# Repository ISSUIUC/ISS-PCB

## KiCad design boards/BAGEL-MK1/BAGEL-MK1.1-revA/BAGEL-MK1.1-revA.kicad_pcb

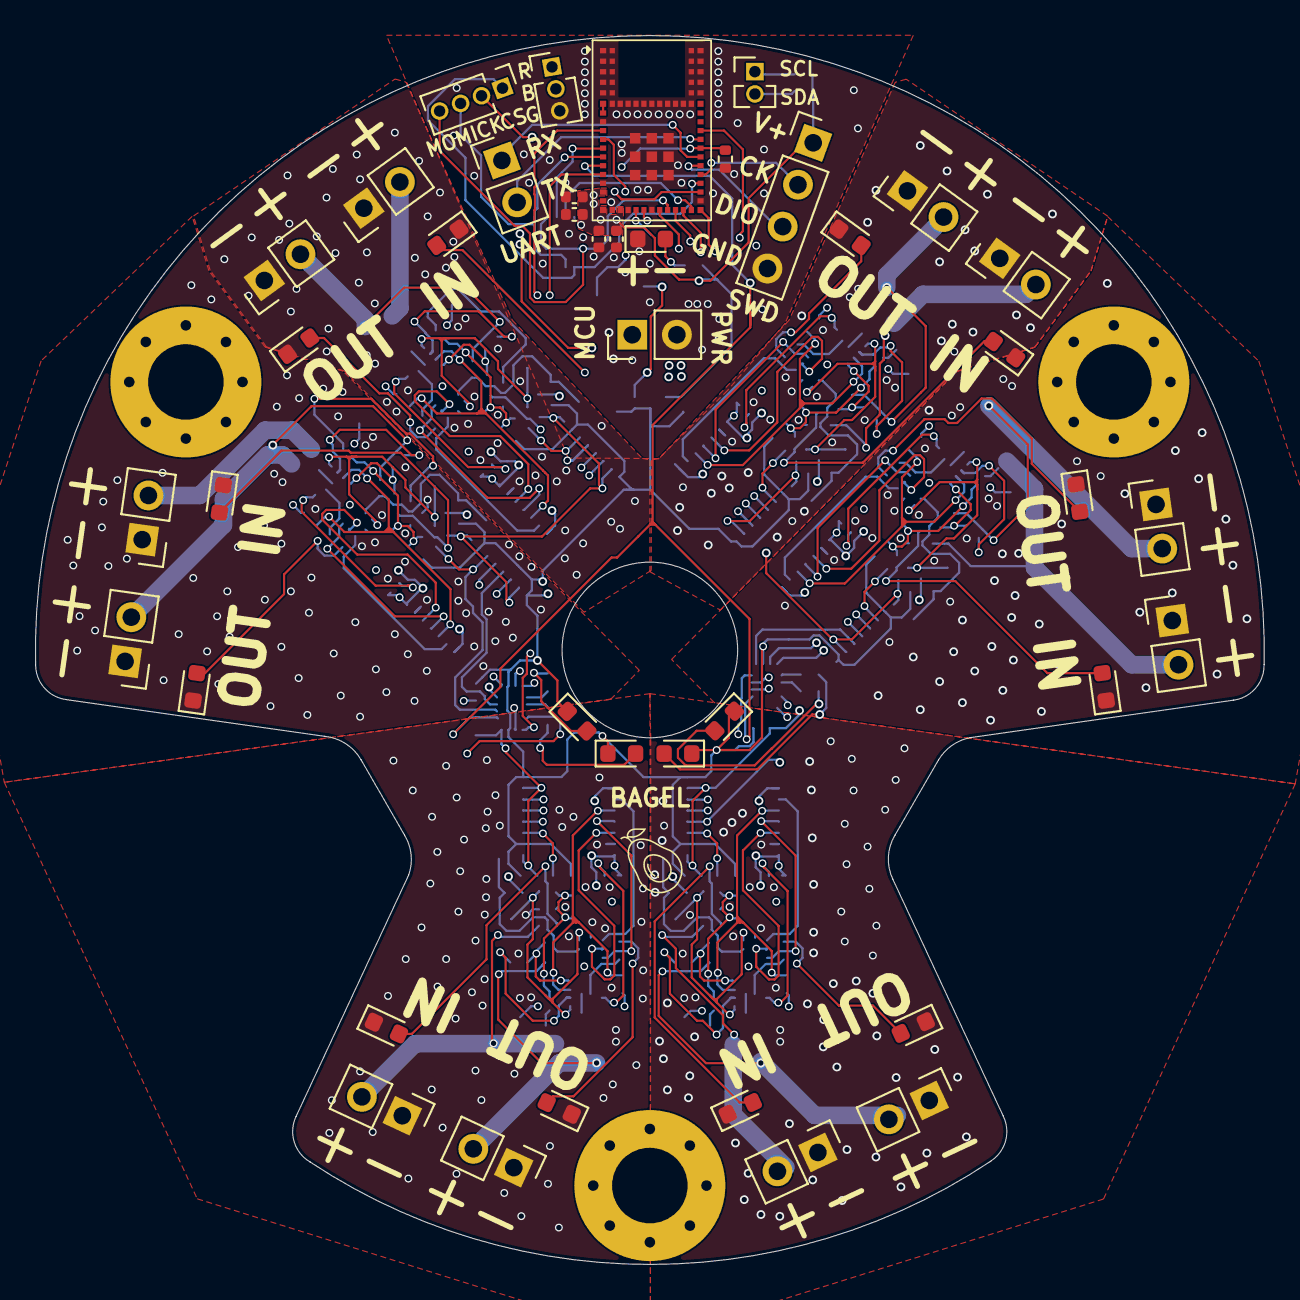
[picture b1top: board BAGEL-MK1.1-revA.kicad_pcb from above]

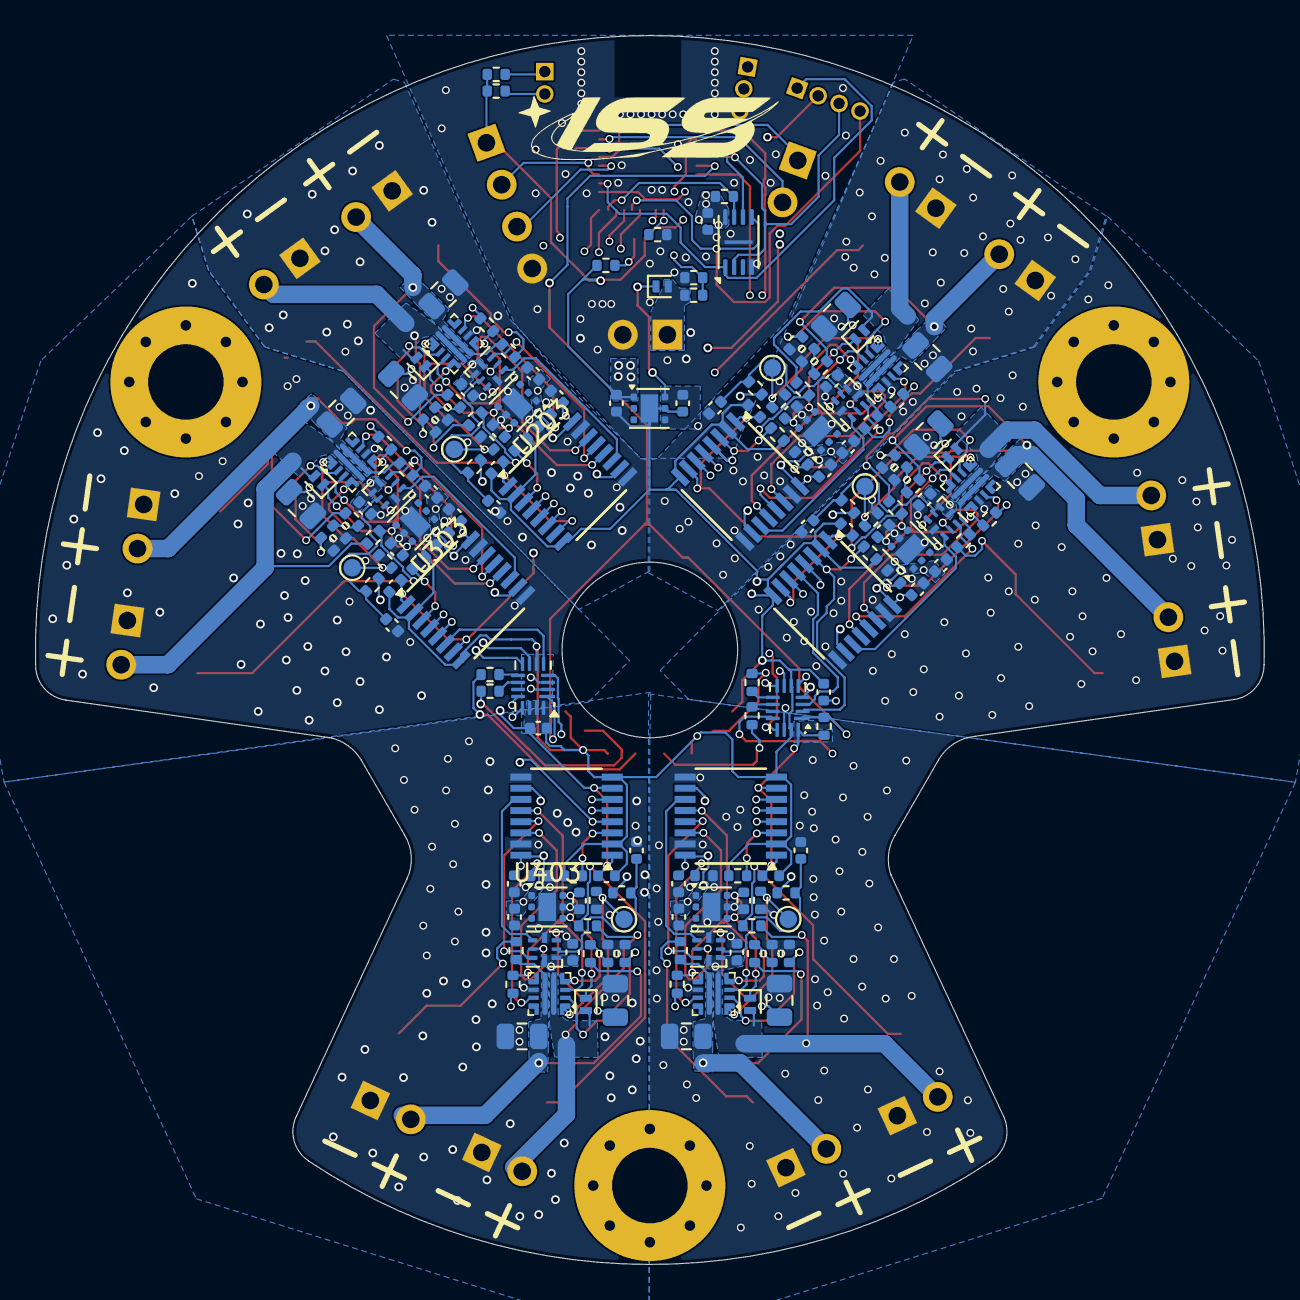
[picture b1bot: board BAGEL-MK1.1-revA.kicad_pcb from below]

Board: 4 copper layers, 70.0 x 70.0 mm, 210 parts (166 on the bottom side), 144 nets.

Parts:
C101, C103, C104, C105, C108, C109, C201, C202, C203, C207, C301, C302, C303, C307, C401, C402, C403, C407, C501, C502, C503, C507, C601, C602, C603, C607, C701, C702, C703, C707: 100nF; C_0402_1005Metric
C102: 4.7uF; C_0402_1005Metric
C106, C204, C304, C404, C504, C604, C704: 1uF; C_0402_1005Metric
C107, C205, C305, C405, C505, C605, C705: 2.2uF; C_0402_1005Metric
C206, C306, C406, C506, C606, C706: 100uF; C_0805_2012Metric
C208, C308, C408, C508, C608, C708: 22uF; C_0805_2012Metric
D101, D201, D301, D401, D501, D601, D701: SDM05U40CSP-7; D_SOD-882
D102, D103, D202, D302, D402, D502, D602, D702: RED; LED_0603_1608Metric
D104: ORANGE; LED_0603_1608Metric
D105, D203, D303, D403, D503, D603, D703: GREEN; LED_0603_1608Metric
D106: BLUE; LED_0603_1608Metric
H101, H102, H103: MountingHole_Pad; MountingHole_4.3mm_M4_Pad_Via
J101, J102, J103, J104, J105, J106, J109, J110, J113, J114, J115, J116, J117, J118: Conn_01x02; PinHeader_1x02_P2.54mm_Vertical
J107: Conn_01x03; PinHeader_1x03_P1.27mm_Vertical
J108: Conn_01x04; PinHeader_1x04_P2.54mm_Vertical
J111: Conn_01x02; PinHeader_1x02_P1.27mm_Vertical
J112: Conn_01x04; PinHeader_1x04_P1.27mm_Vertical
J201, J301, J401, J501, J601, J701: Conn_01x01; TestPoint_Pad_D1.0mm
R101, R102, R103, R113, R201, R202, R204, R205, R301, R302, R304, R305, R401, R402, R404, R405, R501, R502, R504, R505, R601, R602, R604, R605, R701, R702, R704, R705: 10k; R_0402_1005Metric
R104, R105, R106, R107, R108, R109, R112, R203, R303, R403, R503, R603, R703: 4.7k; R_0402_1005Metric
R110, R111: 100k; R_0402_1005Metric
R206, R306, R406, R506, R606, R706: 680; R_0402_1005Metric
R207, R307, R407, R507, R607, R707: 390k; R_0402_1005Metric
R208, R308, R408, R508, R608, R708: 300k; R_0402_1005Metric
R209, R309, R409, R509, R609, R709: 500k; R_0402_1005Metric
R210, R310, R410, R510, R610, R710: 1k; R_0402_1005Metric
U101: W25Q16JLUX; Winbond_USON-8-1EP_3x2mm_P0.5mm_EP0.2x1.6mm
U102: STM32WB1MMC; LGA77_6P5X10_STM
U103, U203, U303, U403, U503, U603, U703: TPS7A25; WSON-6-1EP_2x2mm_P0.65mm_EP1x1.6mm
U104, U105: TCAL9538; UQFN-16_1.8x2.6mm_P0.4mm
U201, U301, U401, U501, U601, U701: ISO7742; SSOP-16_3.9x4.9mm_P0.635mm
U202, U302, U402, U502, U602, U702: SN74AUP1G74RSER; UQFN-RSE0008A
U204, U304, U404, U504, U604, U704: TPS25947; VQFN-HR-RPW0010A

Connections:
/BLUE_LED: R108.1, U105.10 (P7)
/BOOT: J107.2, R102.2, U102.22 (BOOT0)
/CoinCell_V: D101.2 (A), J109.1, R110.2
/EXP_RESET: R103.1, U102.13 (PA2), U104.1 (~RESET), U105.1 (~RESET)
/FLASH_CS: J112.1, U101.1 (~CS), U102.33 (PB4)
/FLASH_RESET: R101.2, U101.7 (~HOLD/~RESET/IO_{3}), U102.29 (PA7)
/GPIO_Clock: R113.2, U102.37 (PA0), U201.4 (INB), U301.4 (INB), U401.4 (INB), U501.4 (INB), U601.4 (INB), U701.4 (INB)
/GREEN_LED: R107.1, U105.9 (P6)
/I2C_SCL: J111.1, R112.1, U102.27 (PB6), U104.12 (SCL), U105.12 (SCL)
/I2C_SDA: J111.2, R109.1, U102.25 (PB7), U104.13 (SDA), U105.13 (SDA)
/NRST: J107.1, U102.23 (NRST)
/ORANGE_LED: R106.1, U104.10 (P7)
/PG_ISO_1: U102.28 (PA3), U201.5 (OUTC)
/PG_ISO_2: U104.7 (P4), U301.5 (OUTC)
/PG_ISO_3: U104.3 (P1), U401.5 (OUTC)
/PG_ISO_4: U105.7 (P4), U501.5 (OUTC)
/PG_ISO_5: U105.3 (P1), U601.5 (OUTC)
/PG_ISO_6: U102.9 (PA4), U701.5 (OUTC)
/RED_LED: R105.1, U104.9 (P6)
/SPI_MISO: J112.3, U101.2 (DO/IO_{1}), U102.12 (PA6)
/SPI_MOSI: J112.4, U101.5 (DI/IO_{0}), U102.26 (PB5)
/SPI_SCK: J112.2, U101.6 (CLK), U102.11 (PA1)
/SWCLK: J108.2, U102.34 (PA14)
/SWDIO: J108.3, U102.35 (PA13)
/SubBatt_GND1: C201.2, C203.2, C204.2, C205.2, C206.2, C207.1, C208.2, D202.1 (K), D203.1 (K), J101.1, J102.1, R202.1, R206.1, R207.2, R209.2, U201.9 (GND2), U201.15 (GND2), U202.4 (GND), U203.5 (GND), U203.7 (Thermal), U204.8 (GND)
/SubBatt_GND2: C301.2, C303.2, C304.2, C305.2, C306.2, C307.1, C308.2, D302.1 (K), D303.1 (K), J103.1, J104.1, R302.1, R306.1, R307.2, R309.2, U301.9 (GND2), U301.15 (GND2), U302.4 (GND), U303.5 (GND), U303.7 (Thermal), U304.8 (GND)
/SubBatt_GND3: C401.2, C403.2, C404.2, C405.2, C406.2, C407.1, C408.2, D402.1 (K), D403.1 (K), J105.1, J106.1, R402.1, R406.1, R407.2, R409.2, U401.9 (GND2), U401.15 (GND2), U402.4 (GND), U403.5 (GND), U403.7 (Thermal), U404.8 (GND)
/SubBatt_GND4: C501.2, C503.2, C504.2, C505.2, C506.2, C507.1, C508.2, D502.1 (K), D503.1 (K), J113.1, J114.1, R502.1, R506.1, R507.2, R509.2, U501.9 (GND2), U501.15 (GND2), U502.4 (GND), U503.5 (GND), U503.7 (Thermal), U504.8 (GND)
/SubBatt_GND5: C601.2, C603.2, C604.2, C605.2, C606.2, C607.1, C608.2, D602.1 (K), D603.1 (K), J115.1, J116.1, R602.1, R606.1, R607.2, R609.2, U601.9 (GND2), U601.15 (GND2), U602.4 (GND), U603.5 (GND), U603.7 (Thermal), U604.8 (GND)
/SubBatt_GND6: C701.2, C703.2, C704.2, C705.2, C706.2, C707.1, C708.2, D702.1 (K), D703.1 (K), J117.1, J118.1, R702.1, R706.1, R707.2, R709.2, U701.9 (GND2), U701.15 (GND2), U702.4 (GND), U703.5 (GND), U703.7 (Thermal), U704.8 (GND)
/SubBatt_V1: D201.2 (A), J101.2, R203.1, U204.5 (IN)
/SubBatt_V2: D301.2 (A), J103.2, R303.1, U304.5 (IN)
/SubBatt_V3: D401.2 (A), J105.2, R403.1, U404.5 (IN)
/SubBatt_V4: D501.2 (A), J113.2, R503.1, U504.5 (IN)
/SubBatt_V5: D601.2 (A), J115.2, R603.1, U604.5 (IN)
/SubBatt_V6: D701.2 (A), J117.2, R703.1, U704.5 (IN)
/Switch 1/PG: R205.2, U201.12 (INC), U204.3 (PG/AUXOFF)
/Switch 1/Q: J201.1, R202.2, U202.3 (Q), U204.1 (EN/UVLO)
/Switch 1/Reg_V: C201.1, C203.1, C205.1, C206.1, R204.1, R205.1, U201.10 (EN2), U201.16 (VCC2), U202.1 (~PRE), U202.8 (VCC), U203.1 (VOUT)
/Switch 1/~CLR: C207.2, R204.2, U202.2 (~CLR)
/Switch 1/~Q: U201.11 (IND), U202.5 (~Q)
/Switch 2/PG: R305.2, U301.12 (INC), U304.3 (PG/AUXOFF)
/Switch 2/Q: J301.1, R302.2, U302.3 (Q), U304.1 (EN/UVLO)
/Switch 2/Reg_V: C301.1, C303.1, C305.1, C306.1, R304.1, R305.1, U301.10 (EN2), U301.16 (VCC2), U302.1 (~PRE), U302.8 (VCC), U303.1 (VOUT)
/Switch 2/~CLR: C307.2, R304.2, U302.2 (~CLR)
/Switch 2/~Q: U301.11 (IND), U302.5 (~Q)
/Switch 3/PG: R405.2, U401.12 (INC), U404.3 (PG/AUXOFF)
/Switch 3/Q: J401.1, R402.2, U402.3 (Q), U404.1 (EN/UVLO)
/Switch 3/Reg_V: C401.1, C403.1, C405.1, C406.1, R404.1, R405.1, U401.10 (EN2), U401.16 (VCC2), U402.1 (~PRE), U402.8 (VCC), U403.1 (VOUT)
/Switch 3/~CLR: C407.2, R404.2, U402.2 (~CLR)
/Switch 3/~Q: U401.11 (IND), U402.5 (~Q)
/Switch 4/PG: R505.2, U501.12 (INC), U504.3 (PG/AUXOFF)
/Switch 4/Q: J501.1, R502.2, U502.3 (Q), U504.1 (EN/UVLO)
/Switch 4/Reg_V: C501.1, C503.1, C505.1, C506.1, R504.1, R505.1, U501.10 (EN2), U501.16 (VCC2), U502.1 (~PRE), U502.8 (VCC), U503.1 (VOUT)
/Switch 4/~CLR: C507.2, R504.2, U502.2 (~CLR)
/Switch 4/~Q: U501.11 (IND), U502.5 (~Q)
/Switch 5/PG: R605.2, U601.12 (INC), U604.3 (PG/AUXOFF)
/Switch 5/Q: J601.1, R602.2, U602.3 (Q), U604.1 (EN/UVLO)
/Switch 5/Reg_V: C601.1, C603.1, C605.1, C606.1, R604.1, R605.1, U601.10 (EN2), U601.16 (VCC2), U602.1 (~PRE), U602.8 (VCC), U603.1 (VOUT)
/Switch 5/~CLR: C607.2, R604.2, U602.2 (~CLR)
/Switch 5/~Q: U601.11 (IND), U602.5 (~Q)
/Switch 6/PG: R705.2, U701.12 (INC), U704.3 (PG/AUXOFF)
/Switch 6/Q: J701.1, R702.2, U702.3 (Q), U704.1 (EN/UVLO)
/Switch 6/Reg_V: C701.1, C703.1, C705.1, C706.1, R704.1, R705.1, U701.10 (EN2), U701.16 (VCC2), U702.1 (~PRE), U702.8 (VCC), U703.1 (VOUT)
/Switch 6/~CLR: C707.2, R704.2, U702.2 (~CLR)
/Switch 6/~Q: U701.11 (IND), U702.5 (~Q)
/Switch_1: R201.1, U102.30 (PA12), U201.3 (INA)
/Switch_2: R301.1, U104.8 (P5), U301.3 (INA)
/Switch_3: R401.1, U104.2 (P0), U401.3 (INA)
/Switch_4: R501.1, U105.8 (P5), U501.3 (INA)
/Switch_5: R601.1, U105.2 (P0), U601.3 (INA)
/Switch_6: R701.1, U102.32 (PA11), U701.3 (INA)
/UART_RX: J110.1, U102.36 (PA10)
/UART_TX: J110.2, U102.38 (PA9)
/V_SENSE: R110.1, R111.2, U102.10 (PA8)
/V_out_1: C208.1, J102.2, R208.1, R210.1, U204.6 (OUT)
/V_out_2: C308.1, J104.2, R308.1, R310.1, U304.6 (OUT)
/V_out_3: C408.1, J106.2, R408.1, R410.1, U404.6 (OUT)
/V_out_4: C508.1, J114.2, R508.1, R510.1, U504.6 (OUT)
/V_out_5: C608.1, J116.2, R608.1, R610.1, U604.6 (OUT)
/V_out_6: C708.1, J118.2, R708.1, R710.1, U704.6 (OUT)
/~Q_ISO_1: U102.39 (PA5), U201.6 (OUTD)
/~Q_ISO_2: U104.5 (P3), U301.6 (OUTD)
/~Q_ISO_3: U104.4 (P2), U401.6 (OUTD)
/~Q_ISO_4: U105.5 (P3), U501.6 (OUTD)
/~Q_ISO_5: U105.4 (P2), U601.6 (OUTD)
/~Q_ISO_6: U102.14 (PB8), U701.6 (OUTD)
MCU_GND: C101.2, C102.2, C103.2, C104.2, C105.2, C106.2, C107.2, C108.2, C109.2, C202.2, C302.2, C402.2, C502.2, C602.2, C702.2, D102.1 (K), D103.1 (K), D104.1 (K), D105.1 (K), D106.1 (K), J107.3, J108.4, J109.2, R102.1, R111.1, R113.1, R201.2, R301.2, R401.2, R501.2, R601.2, R701.2, U101.4 (GND), U101.9 (EP), U102.1 (VSS), U102.2 (VSS), U102.3 (VSS), U102.4 (VSS), U102.5 (VSSRF), U102.8 (VSSRF), U102.15 (VSS), U102.17 (VSS), U102.19 (VSS), U102.21 (VSSSMPS), U102.24 (VSS), U102.31 (VSS), U102.43 (VSS), U102.44 (VSS), U102.45 (VSS), U102.46 (VSS), U102.47 (VSS), U102.48 (VSS), U102.49 (VSS), U102.50 (VSS), U102.51 (VSS), U102.52 (VSS), U102.53 (VSS), U102.54 (VSS), U102.55 (VSS), U102.56 (VSS), U102.57 (VSS), U102.58 (VSS), U102.59 (VSS), U102.60 (VSS), U102.61 (VSS), U102.62 (VSS), U102.63 (VSS), U102.64 (VSS), U102.65 (VSS), U102.66 (VSS), U102.67 (VSS), U102.68 (VSS), U102.69 (VSS), U102.70 (VSS), U102.71 (VSS), U102.72 (VSS), U102.73 (VSS), U102.74 (VSS), U102.75 (VSS), U102.76 (VSS), U102.77 (VSS), U103.5 (GND), U103.7 (Thermal), U104.6 (GND), U104.16 (A1), U105.6 (GND), U105.15 (A0), U201.2 (GND1), U201.8 (GND1), U301.2 (GND1), U301.8 (GND1), U401.2 (GND1), U401.8 (GND1), U501.2 (GND1), U501.8 (GND1), U601.2 (GND1), U601.8 (GND1), U701.2 (GND1), U701.8 (GND1)
MCU_V: C101.1, C102.1, C103.1, C104.1, C105.1, C107.1, C108.1, C109.1, C202.1, C302.1, C402.1, C502.1, C602.1, C702.1, J108.1, R101.1, R103.2, R104.2, R109.2, R112.2, U101.8 (VCC), U102.16 (VDDA), U102.18 (VBAT), U102.20 (VDDSMPS), U103.1 (VOUT), U104.14 (VCC), U104.15 (A0), U105.14 (VCC), U105.16 (A1), U201.1 (VCC1), U201.7 (EN1), U301.1 (VCC1), U301.7 (EN1), U401.1 (VCC1), U401.7 (EN1), U501.1 (VCC1), U501.7 (EN1), U601.1 (VCC1), U601.7 (EN1), U701.1 (VCC1), U701.7 (EN1)
unnamed: C106.1, D101.1 (K), U103.4 (EN), U103.6 (VIN)
unnamed: D102.2 (A), R104.1
unnamed: D103.2 (A), R105.2
unnamed: D104.2 (A), R106.2
unnamed: D105.2 (A), R107.2
unnamed: D106.2 (A), R108.2
unnamed: C204.1, D201.1 (K), U203.4 (EN), U203.6 (VIN)
unnamed: D202.2 (A), R203.2
unnamed: D203.2 (A), R210.2
unnamed: C304.1, D301.1 (K), U303.4 (EN), U303.6 (VIN)
unnamed: D302.2 (A), R303.2
unnamed: D303.2 (A), R310.2
unnamed: C404.1, D401.1 (K), U403.4 (EN), U403.6 (VIN)
unnamed: D402.2 (A), R403.2
unnamed: D403.2 (A), R410.2
unnamed: C504.1, D501.1 (K), U503.4 (EN), U503.6 (VIN)
unnamed: D502.2 (A), R503.2
unnamed: D503.2 (A), R510.2
unnamed: C604.1, D601.1 (K), U603.4 (EN), U603.6 (VIN)
unnamed: D602.2 (A), R603.2
unnamed: D603.2 (A), R610.2
unnamed: C704.1, D701.1 (K), U703.4 (EN), U703.6 (VIN)
unnamed: D702.2 (A), R703.2
unnamed: D703.2 (A), R710.2
unnamed: U102.6 (ANT_IN), U102.7 (ANT_OUT)
unnamed: U201.14 (OUTA), U202.6 (D)
unnamed: U201.13 (OUTB), U202.7 (CLK)
unnamed: R206.2, U204.9 (ILM)
unnamed: R207.1, U204.2 (OVLO/OVCSEL)
unnamed: R208.2, R209.1, U204.4 (PGTH/NFLT)
unnamed: U301.14 (OUTA), U302.6 (D)
unnamed: U301.13 (OUTB), U302.7 (CLK)
unnamed: R306.2, U304.9 (ILM)
unnamed: R307.1, U304.2 (OVLO/OVCSEL)
unnamed: R308.2, R309.1, U304.4 (PGTH/NFLT)
unnamed: U401.14 (OUTA), U402.6 (D)
unnamed: U401.13 (OUTB), U402.7 (CLK)
unnamed: R406.2, U404.9 (ILM)
unnamed: R407.1, U404.2 (OVLO/OVCSEL)
unnamed: R408.2, R409.1, U404.4 (PGTH/NFLT)
unnamed: U501.14 (OUTA), U502.6 (D)
unnamed: U501.13 (OUTB), U502.7 (CLK)
unnamed: R506.2, U504.9 (ILM)
unnamed: R507.1, U504.2 (OVLO/OVCSEL)
unnamed: R508.2, R509.1, U504.4 (PGTH/NFLT)
unnamed: U601.14 (OUTA), U602.6 (D)
unnamed: U601.13 (OUTB), U602.7 (CLK)
unnamed: R606.2, U604.9 (ILM)
unnamed: R607.1, U604.2 (OVLO/OVCSEL)
unnamed: R608.2, R609.1, U604.4 (PGTH/NFLT)
unnamed: U701.14 (OUTA), U702.6 (D)
unnamed: U701.13 (OUTB), U702.7 (CLK)
unnamed: R706.2, U704.9 (ILM)
unnamed: R707.1, U704.2 (OVLO/OVCSEL)
unnamed: R708.2, R709.1, U704.4 (PGTH/NFLT)

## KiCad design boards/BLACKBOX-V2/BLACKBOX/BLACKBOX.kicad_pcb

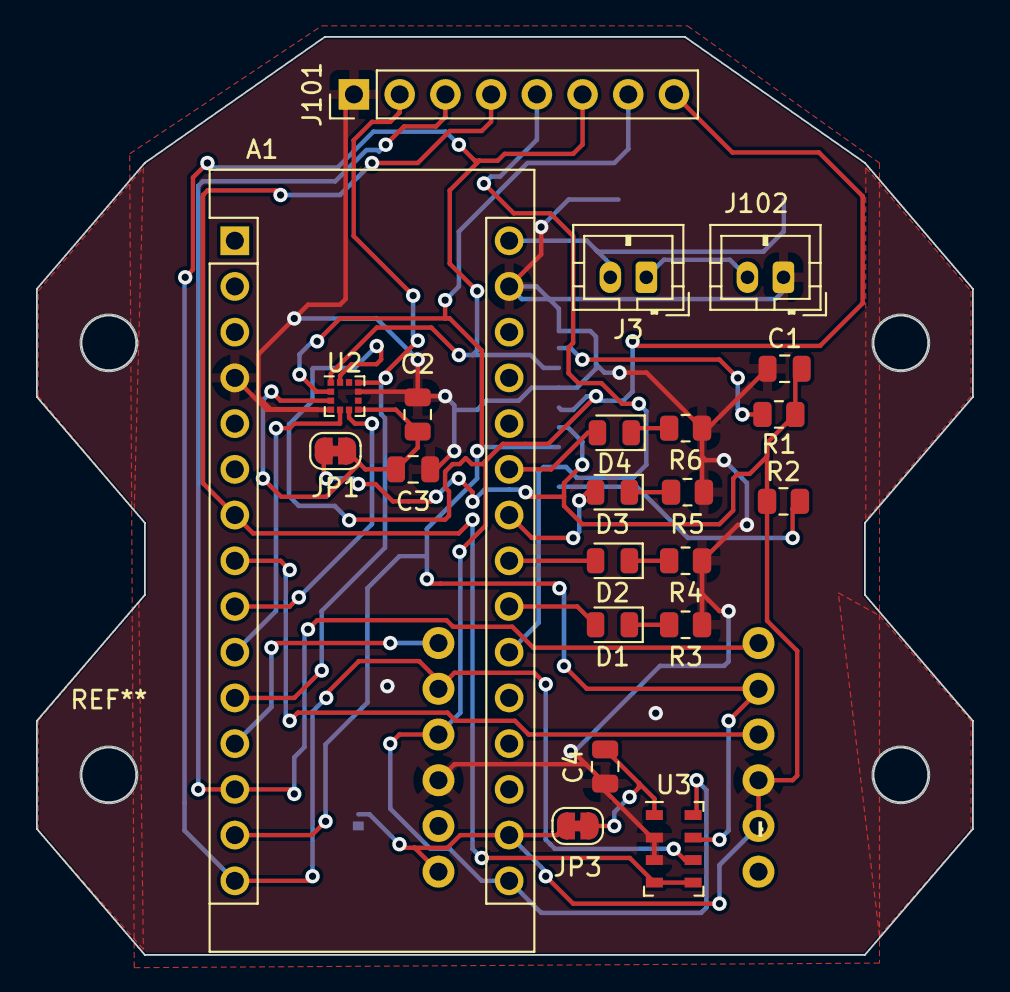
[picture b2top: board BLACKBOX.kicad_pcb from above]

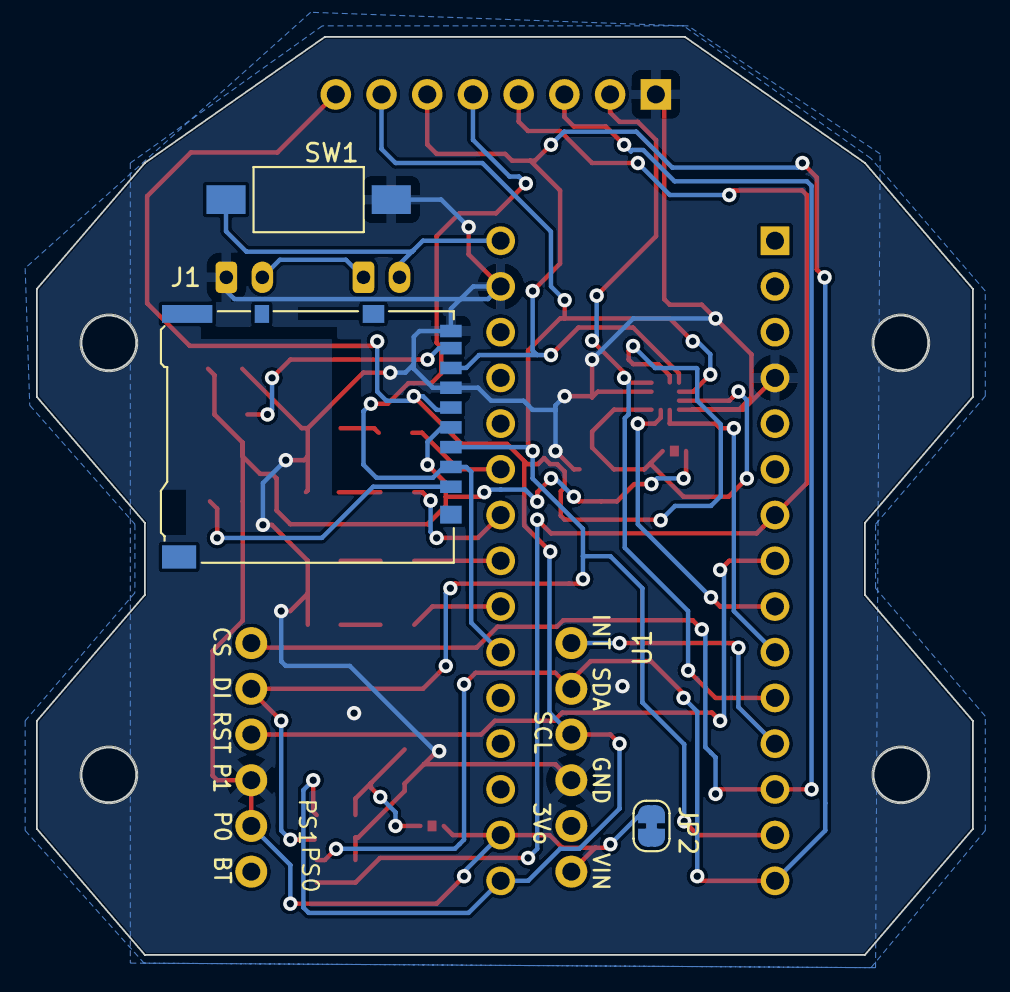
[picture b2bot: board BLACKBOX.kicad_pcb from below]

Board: 2 copper layers, 52.0 x 51.0 mm, 26 parts (4 on the bottom side), 27 nets.

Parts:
A1: Arduino_Nano_v3.x; Arduino_Nano
C1: 100 nF; C_0805_2012Metric
C2, C3, C4: 100nF; C_0805_2012Metric
D1: GREEN; LED_0805_2012Metric
D2: ORANGE; LED_0805_2012Metric
D3: BLUE; LED_0805_2012Metric
D4: RED; LED_0805_2012Metric
J1: Micro_SD_Card; microSD_HC_Hirose_DM3AT-SF-PEJM5
J3, J102: Conn_01x02_Female; JST_PH_B2B-PH-K_1x02_P2.00mm_Vertical
J101: Conn_01x08_Female; PinHeader_1x08_P2.54mm_Vertical
JP1, JP2, JP3: Jumper_NC_Small; SolderJumper-2_P1.3mm_Bridged_RoundedPad1.0x1.5mm
R1, R2, R3, R4, R5, R6: 10k; R_0805_2012Metric
SW1: SW_Push; SW_SPST_FSMSM
U1: Adafruit-BNO085; Adafruit_BNO805
U2: KX122-1042; LGA-12_2x2mm_P0.5mm
U3: MS5611-01BA; LGA-8_3x5mm_P1.25mm

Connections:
+3V3: A1.17 (3V3), C1.2, J1.4 (VDD), JP1.1, JP2.2, JP3.1, R1.1, R2.1, U1.1 (VIN), U1.2 (3Vo), U1.3 (GND)
/BNO_CS: A1.13 (D10), J101.3, U1.6 (INT)
/BNO_INT: A1.12 (D9), U1.6 (INT)
/BNO_RST: A1.8 (D5), U1.4 (SCL)
/KX_CS: A1.11 (D8), J101.2, U2.10 (~CS)
/KX_INT1: A1.10 (D7), U2.5 (INT1)
/KX_INT2: A1.9 (D6), U2.6 (INT2)
/LED0: A1.22 (A3), D1.2 (A)
/LED1: A1.23 (A4), D2.2 (A)
/LED2: A1.24 (A5), D3.2 (A)
/LED3: A1.25 (A6), D4.2 (A)
/MISO: A1.15 (D12), J1.7 (DAT0), J101.6, U1.5 (SDA), U2.1 (SDO/ADDR), U3.6 (SDO)
/MOSI: A1.14 (D11), J1.3 (CMD), J101.7, U1.5 (SDA), U2.2 (SDI/SDA), U3.7 (SDI/SDA)
/MS_CS: A1.7 (D4), J101.4, U3.4 (CSB), U3.5 (CSB)
/SCK: A1.16 (D13), J1.5 (CLK), J101.8, U1.4 (SCL), U2.12 (SCLK/SCL), U3.8 (SCLK)
/SD_CS: A1.21 (A2), J1.2 (DAT3/CD), J101.5
GND: A1.4 (GND), A1.29 (GND), C1.1, C2.2, C3.2, C4.1, J1.6 (VSS), J1.9 (SHIELD), J101.1, J102.1, R3.2, R4.2, R5.2, R6.2, SW1.2, U1.3 (GND), U2.4 (TRIG), U2.9 (GND), U3.2 (PS), U3.3 (GND)
unnamed: C2.1, C3.1, JP1.2, U2.3 (IO_VDD), U2.7 (VDD)
unnamed: C4.2, JP3.2, U3.1 (VDD)
unnamed: D1.1 (K), R3.1
unnamed: D2.1 (K), R4.1
unnamed: D3.1 (K), R5.1
unnamed: D4.1 (K), R6.1
unnamed: J1.1 (DAT2), R2.2
unnamed: J1.8 (DAT1), R1.2
VBUS: J3.1, J102.2
VCC: A1.30 (VIN), J3.2, SW1.1

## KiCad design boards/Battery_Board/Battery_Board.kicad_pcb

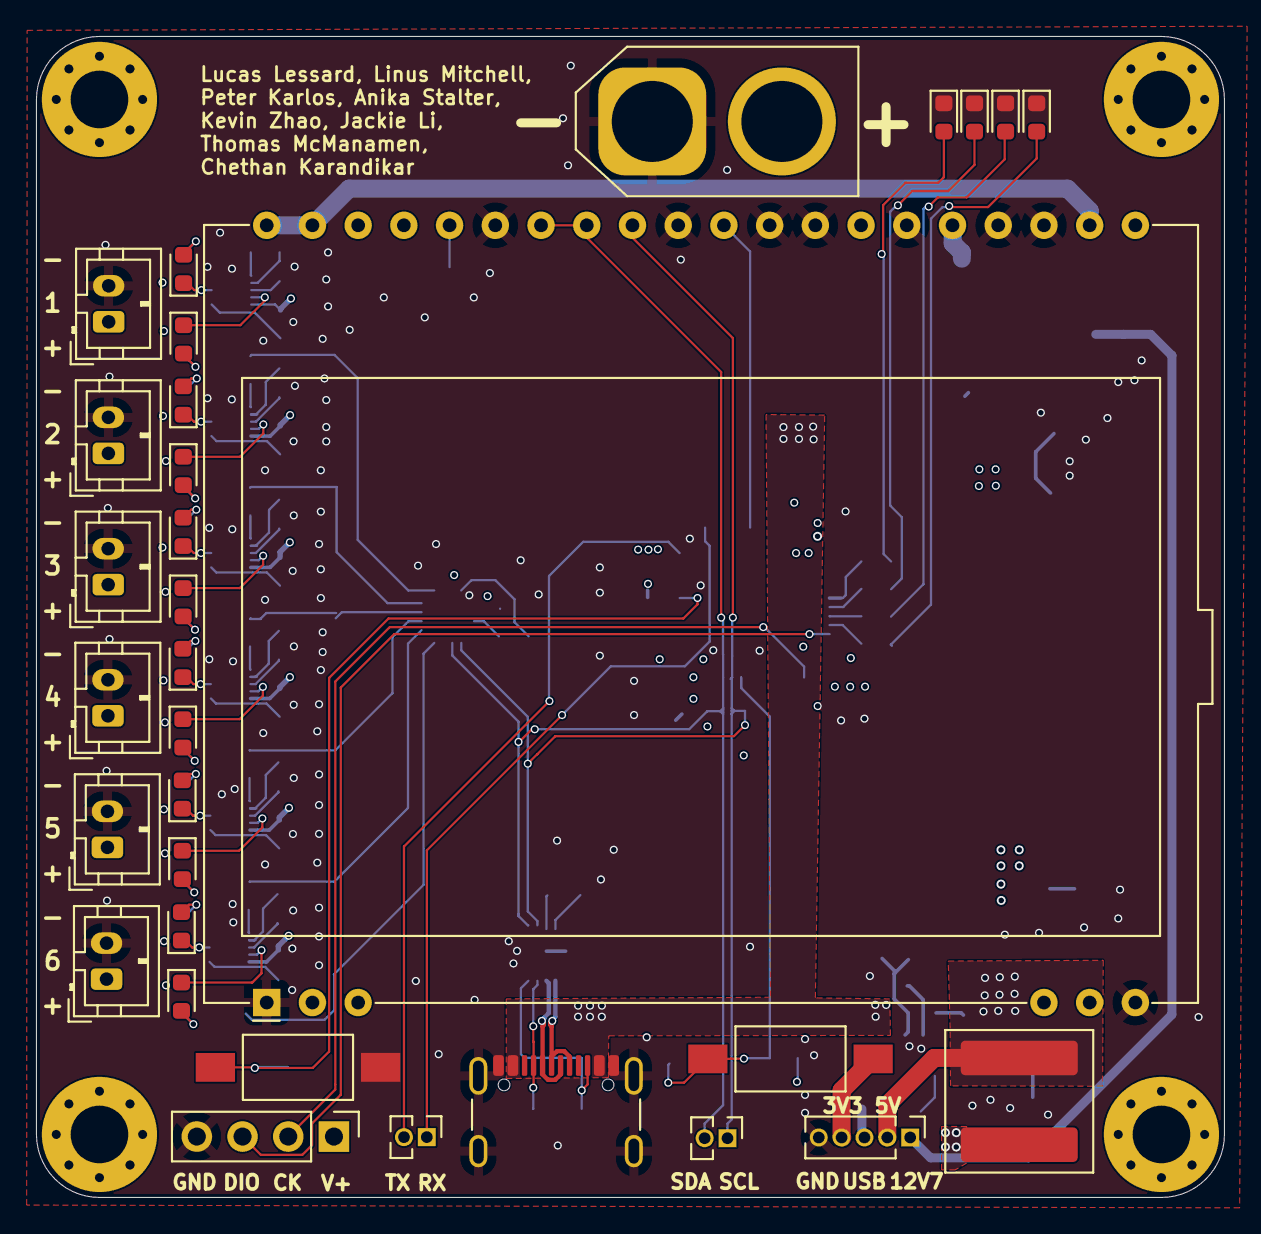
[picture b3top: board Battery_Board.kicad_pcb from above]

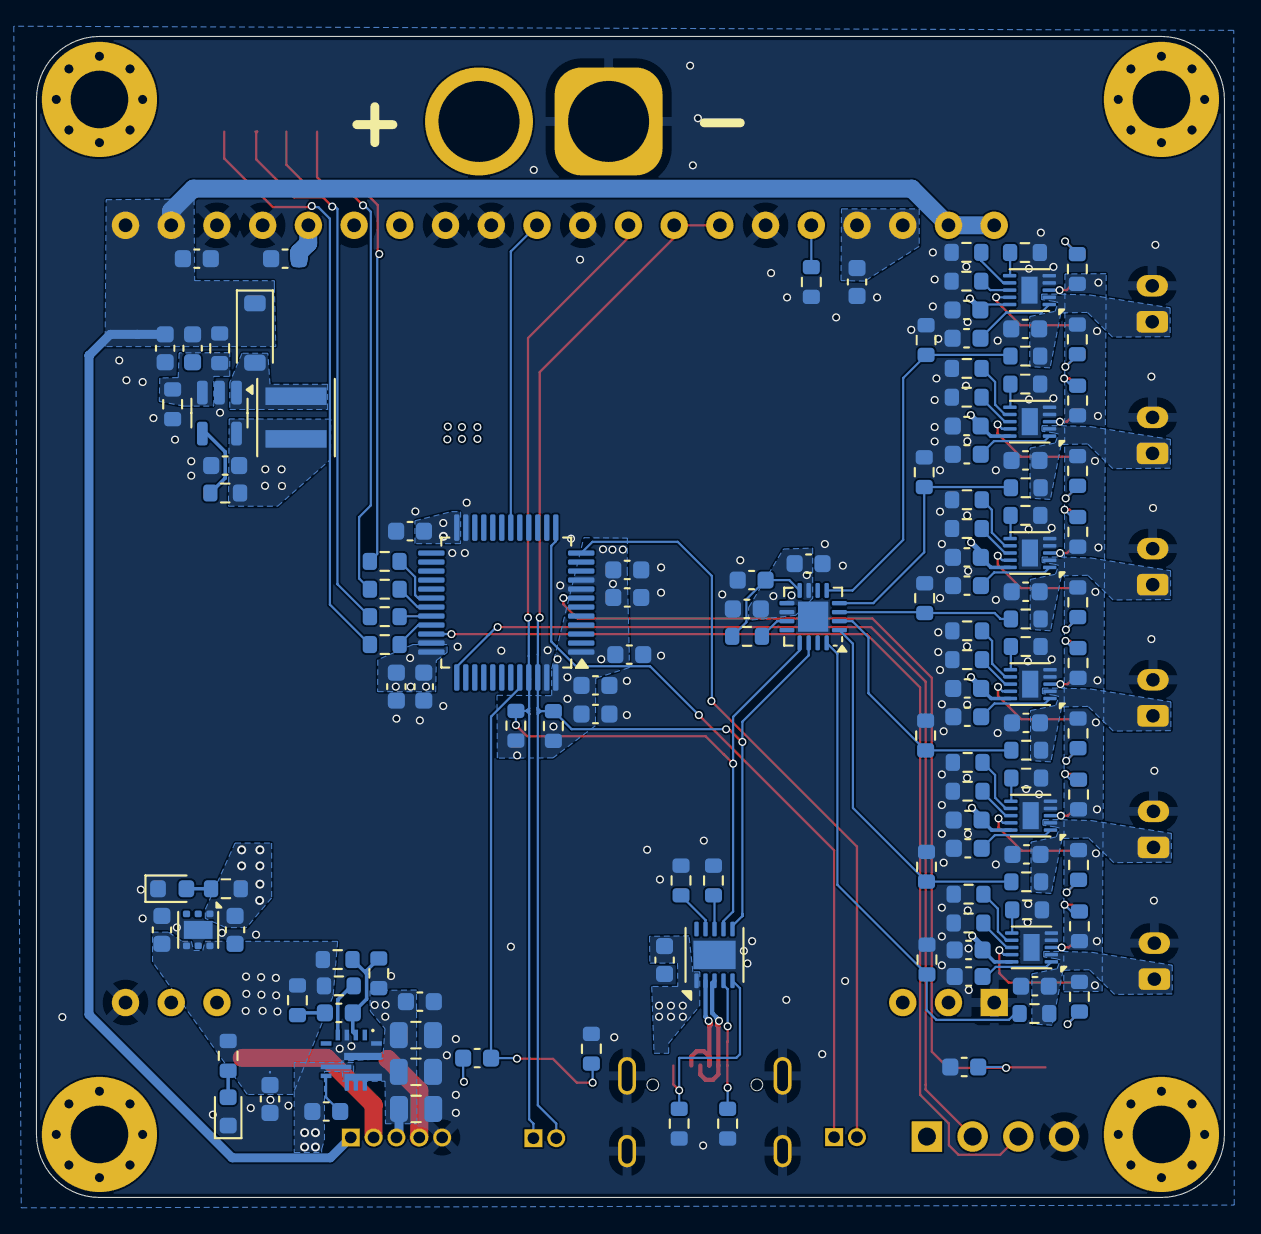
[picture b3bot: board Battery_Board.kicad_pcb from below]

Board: 4 copper layers, 66.0 x 64.5 mm, 163 parts (127 on the bottom side), 102 nets.

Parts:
C101, C102, C103, C104, C107, C112, C115, C201, C202, C301, C302, C401, C402, C501, C502, C601, C602, C701, C702: 1uF; C_0603_1608Metric
C105: 10nF; C_0603_1608Metric
C106, C108, C109, C111, C118, C121, C122, C123, C125, C128: 100nF; C_0603_1608Metric
C110, C113, C117: 4.7uF; C_0805_2012Metric
C114, C119, C124: 2.2uF; C_0603_1608Metric
C116, C120, C127, C203, C303, C403, C503, C603, C703: 10uF; C_0603_1608Metric
C126: 100pF; C_0603_1608Metric
C129: 47uF; C_0603_1608Metric
D101, D103: RED; LED_0603_1608Metric
D102: MBR0540; D_SOD-123
D104: GREEN; LED_0603_1608Metric
D105: BLUE; LED_0603_1608Metric
D106: RED LED; LED_0603_1608Metric
D107: ORANGE; LED_0603_1608Metric
D201, D301, D401, D501, D601, D701: Red; LED_0603_1608Metric
D202, D302, D402, D502, D602, D702: Green; LED_0603_1608Metric
H101, H102, H103, H104: MountingHole; MountingHole_3.2mm_M3_Pad_Via
J101: USB4105-GF-A; USB_C_Receptacle_GCT_USB4105-xx-A_16P_TopMnt_Horizontal
J102: Conn_01x04; PinHeader_1x04_P2.54mm_Vertical
J103, J104: Conn_01x02; PinHeader_1x02_P1.27mm_Vertical
J105: XT60; AMASS_XT60-M_1x02_P7.20mm_Vertical
J106: Conn_01x05; PinHeader_1x05_P1.27mm_Vertical
J201, J301, J401, J501, J601, J701: Conn_01x02; JST_PH_B2B-PH-K_1x02_P2.00mm_Vertical
L101: 10uH; L_Coilcraft_XxL4040
L102: 3.3uH; L_Coilcraft_XAL7070-XXX
R101, R102, R103, R104, R105, R106, R107, R108, R109, R112, R113, R114, R115, R122: 100k; R_0603_1608Metric
R110, R117: 5.1k; R_0603_1608Metric
R111: VSET; R_0603_1608Metric
R116: ISET; R_0603_1608Metric
R118, R125, R129, R130, R131, R132, R204, R205, R304, R305, R404, R405, R504, R505, R604, R605, R704, R705: 470; R_0603_1608Metric
R119, R120, R128, R201, R301, R401, R501, R601, R701: 10k; R_0603_1608Metric
R121: 910K; R_0603_1608Metric
R123: 75k; R_0603_1608Metric
R124: 8.2k; R_0603_1608Metric
R126: 20k; R_0603_1608Metric
R127: 73.2k; R_0603_1608Metric
R133, R134: 4.7k; R_0603_1608Metric
R202, R302, R402, R502, R602, R702: 18k; R_0603_1608Metric
R203, R303, R403, R503, R603, R703: 604; R_0603_1608Metric
SW101, SW102: SW_Push; SW_SPST_FSMSM
U101: ADS7138-Q1; WQFN-16-1EP_3x3mm_P0.5mm_EP1.68x1.68mm
U102: HUSB238; DFN-10-1EP_3x3mm_P0.5mm_EP1.58x2.35mm
U103: STM32L412CBTx; LQFP-48_7x7mm_P0.5mm
U104: TPS7A26; WSON-6-1EP_2x2mm_P0.65mm_EP1x1.6mm
U105: OLEDM128-6; EA_DOGM128-6
U106: TI_TPS56637; VQFN-HR-RPA0010A
U107: LT1935; TSOT-23-5
U201, U301, U401, U501, U601, U701: BQ25185; Texas_DLH0010A_WSON-10-1EP_2.2x2mm_P0.4mm_EP0.9x1.5mm

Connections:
12.7V: C119.2, C127.1, C128.1, D102.1 (K), J106.1, R123.2, U105.21 (VCC), U105.22 (VCC), U105.39 (VCC), U105.40 (VCC)
+3V3: C103.1, C104.1, C105.1, C106.1, C108.1, C109.1, C111.1, C112.1, C114.1, C115.1, C116.1, C121.2, C123.2, J102.1, J106.4, R118.2, R133.2, R134.2, SW101.2, U101.7 (AVDD), U101.10 (DVDD), U103.1 (VBAT), U103.9 (VDDA), U103.24 (VDD), U103.36 (VDDUSB), U103.48 (VDD), U104.1 (VOUT), U105.25 (VDD), U105.27 (BS1)
/5V: C107.1, C120.1, C129.2, C201.2, C301.2, C401.2, C501.2, C601.2, C701.2, J106.2, L101.1, L102.2, R120.2, R122.2, R126.2, R127.1, R131.1, R204.1, R205.1, R304.1, R305.1, R404.1, R405.1, R504.1, R505.1, R604.1, R605.1, R704.1, R705.1, U104.4 (EN), U104.6 (VIN), U107.5 (VIN), U201.10 (IN), U301.10 (IN), U401.10 (IN), U501.10 (IN), U601.10 (IN), U701.10 (IN)
/BATT_1_V: C202.2, J201.1, R101.1, U201.2 (BAT)
/BATT_1_V_SENSE: R101.2, R102.1, U101.5 (AIN6/GPIO6)
/BATT_2_V: C302.2, J301.1, R106.1, U301.2 (BAT)
/BATT_2_V_SENSE: R106.2, R107.1, U101.4 (AIN5/GPIO5)
/BATT_3_V: C402.2, J401.1, R112.1, U401.2 (BAT)
/BATT_3_V_SENSE: R112.2, R113.1, U101.3 (AIN4/GPIO4)
/BATT_4_V: C502.2, J501.1, R103.1, U501.2 (BAT)
/BATT_4_V_SENSE: R103.2, R104.1, U101.2 (AIN3/GPIO3)
/BATT_5_V: C602.2, J601.1, R108.1, U601.2 (BAT)
/BATT_5_V_SENSE: R108.2, R109.1, U101.1 (ANI2/GPIO2)
/BATT_6_V: C702.2, J701.1, R114.1, U701.2 (BAT)
/BATT_6_V_SENSE: R114.2, R115.1, U101.16 (AIN1/GPIO1)
/BOOT0: C121.1, R119.1, SW101.1, U103.44 (PH3)
/Boot: C125.1, U106.7 (BOOT)
/D+: J101.A6 (D+), J101.B6 (D+), U102.2 (D+)
/D-: J101.A7 (D-), J101.B7 (D-), U102.3 (D-)
/Debug_LED_BLUE: R130.1, U103.33 (PA12)
/Debug_LED_GREEN: R129.1, U103.32 (PA11)
/Debug_LED_ORANGE: R132.1, U103.31 (PA10)
/Debug_LED_RED: R125.1, U103.30 (PA9)
/FB: C126.1, R127.2, R128.1, U106.2 (FB)
/I2C_SCL: J104.1, R133.1, U101.13 (SCL), U102.7 (SCL), U103.45 (PB8), U105.32 (D0)
/I2C_SDA: J104.2, R134.1, U101.14 (SDA), U102.6 (SDA), U103.46 (PB9), U105.33 (D1), U105.34 (D2)
/LPUART_RX: J103.1, U103.13 (PA3)
/LPUART_TX: J103.2, U103.12 (PA2)
/NRST: C122.1, SW102.1, U103.7 (NRST)
/OLED_RES: U103.18 (PB0), U105.30 (~RES)
/SWCLK: J102.2, U103.37 (PA14)
/SWDIO: J102.3, U103.34 (PA13)
/USB_CC1: J101.A5 (CC1), R117.2, U102.4 (CC1)
/USB_CC2: J101.B5 (CC2), R110.2, U102.5 (CC2)
/USB_POWER: C101.2, C110.1, C113.1, C117.1, C118.1, J101.A4 (VBUS), J101.A9 (VBUS), J101.B4 (VBUS), J101.B9 (VBUS), J105.2, J106.3, U102.1 (VIN), U106.8 (VIN)
GND: C101.1, C102.2, C103.2, C104.2, C105.2, C106.2, C107.2, C108.2, C109.2, C110.2, C111.2, C112.2, C113.2, C114.2, C115.2, C116.2, C117.2, C118.2, C119.1, C120.2, C122.2, C123.1, C124.2, C127.2, C128.2, C129.1, C201.1, C202.1, C203.2, C301.1, C302.1, C303.2, C401.1, C402.1, C403.2, C501.1, C502.1, C503.2, C601.1, C602.1, C603.2, C701.1, C702.1, C703.2, D101.1 (K), D103.1 (K), D104.1 (K), D105.1 (K), D106.1 (K), D107.1 (K), J101.A1 (GND), J101.A12 (GND), J101.B1 (GND), J101.B12 (GND), J101.S1 (SHIELD), J102.4, J105.1, J106.5, J201.2, J301.2, J401.2, J501.2, J601.2, J701.2, R102.2, R104.2, R107.2, R109.2, R110.1, R111.2, R113.2, R115.2, R116.2, R117.1, R119.2, R121.2, R124.2, R128.2, R201.2, R202.2, R203.1, R301.2, R302.2, R303.1, R401.2, R402.2, R403.1, R501.2, R502.2, R503.1, R601.2, R602.2, R603.1, R701.2, R702.2, R703.1, SW102.2, U101.9 (GND), U101.17 (EPAD), U102.11 (GND), U103.8 (VSSA), U103.23 (VSS), U103.35 (VSS), U103.47 (VSS), U104.5 (GND), U104.7 (Thermal), U105.1 (ESD_GND), U105.20 (ESD_GND), U105.23 (GND), U105.24 (GND), U105.26 (BS0), U105.28 (GND), U105.29 (~CS), U105.31 (D/C), U105.35 (GND), U106.3 (AGND), U106.9 (PGND), U106.10 (MODE), U107.2 (GND), U201.4 (/CE), U201.5 (GND), U201.11 (EPAD), U301.4 (/CE), U301.5 (GND), U301.11 (EPAD), U401.4 (/CE), U401.5 (GND), U401.11 (EPAD), U501.4 (/CE), U501.5 (GND), U501.11 (EPAD), U601.4 (/CE), U601.5 (GND), U601.11 (EPAD), U701.4 (/CE), U701.5 (GND), U701.11 (EPAD)
unnamed: C124.1, U105.37 (VCOMH), U105.38 (VCOMH)
unnamed: C126.2, R126.1
unnamed: D101.2 (A), R118.1
unnamed: D102.2 (A), L101.2, U107.1 (SW)
unnamed: D103.2 (A), R125.2
unnamed: D104.2 (A), R129.2
unnamed: D105.2 (A), R130.2
unnamed: D106.2 (A), R131.2
unnamed: D107.2 (A), R132.2
unnamed: D201.2 (A), R204.2
unnamed: D201.1 (K), U201.9 (STAT1)
unnamed: D202.2 (A), R205.2
unnamed: D202.1 (K), U201.3 (STAT2)
unnamed: D301.2 (A), R304.2
unnamed: D301.1 (K), U301.9 (STAT1)
unnamed: D302.2 (A), R305.2
unnamed: D302.1 (K), U301.3 (STAT2)
unnamed: D401.2 (A), R404.2
unnamed: D401.1 (K), U401.9 (STAT1)
unnamed: D402.2 (A), R405.2
unnamed: D402.1 (K), U401.3 (STAT2)
unnamed: D501.2 (A), R504.2
unnamed: D501.1 (K), U501.9 (STAT1)
unnamed: D502.2 (A), R505.2
unnamed: D502.1 (K), U501.3 (STAT2)
unnamed: D601.2 (A), R604.2
unnamed: D601.1 (K), U601.9 (STAT1)
unnamed: D602.2 (A), R605.2
unnamed: D602.1 (K), U601.3 (STAT2)
unnamed: D701.2 (A), R704.2
unnamed: D701.1 (K), U701.9 (STAT1)
unnamed: D702.2 (A), R705.2
unnamed: D702.1 (K), U701.3 (STAT2)
unnamed: R105.1, U101.11 (ADDR)
unnamed: C102.1, R105.2, U101.8 (DECAP)
unnamed: R116.1, U102.9 (ISET)
unnamed: R111.1, U102.8 (VSET)
unnamed: R121.1, U105.36 (IREF)
unnamed: R122.1, U106.4 (PG)
unnamed: C125.2, L102.1, U106.6 (SW)
unnamed: R123.1, R124.1, U107.3 (FB)
unnamed: R120.1, U107.4 (~SHDN)
unnamed: R202.1, U201.7 (ILIM/VSET)
unnamed: R203.2, U201.8 (ISET)
unnamed: C203.1, U201.1 (SYS)
unnamed: R201.1, U201.6 (TS/MR)
unnamed: R302.1, U301.7 (ILIM/VSET)
unnamed: R303.2, U301.8 (ISET)
unnamed: C303.1, U301.1 (SYS)
unnamed: R301.1, U301.6 (TS/MR)
unnamed: R402.1, U401.7 (ILIM/VSET)
unnamed: R403.2, U401.8 (ISET)
unnamed: C403.1, U401.1 (SYS)
unnamed: R401.1, U401.6 (TS/MR)
unnamed: R502.1, U501.7 (ILIM/VSET)
unnamed: R503.2, U501.8 (ISET)
unnamed: C503.1, U501.1 (SYS)
unnamed: R501.1, U501.6 (TS/MR)
unnamed: R602.1, U601.7 (ILIM/VSET)
unnamed: R603.2, U601.8 (ISET)
unnamed: C603.1, U601.1 (SYS)
unnamed: R601.1, U601.6 (TS/MR)
unnamed: R702.1, U701.7 (ILIM/VSET)
unnamed: R703.2, U701.8 (ISET)
unnamed: C703.1, U701.1 (SYS)
unnamed: R701.1, U701.6 (TS/MR)
